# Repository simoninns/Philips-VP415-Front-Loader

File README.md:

# Philips-VP415-Front-Loader
Replacement front-loader module (P) for the Philips VP415 Domesday LaserVision player

For more information, please see [the project wiki](https://github.com/simoninns/Philips-VP415-Front-Loader/wiki)

## Synopsis

This card is designed as a drop-in replacement for the original Philips VP415 LaserVision player's front-loader module (P).

## Motivation

The original front loader module uses custom Philips microswitches which can no longer be sourced.  The front-loader module is responsible for detecting the closure of the disc tray and the switches are impacted everytime a LaserDisc is loaded making it a common failure point in VP415s.  In addition, since the disc tray can vibrate during transport, the front-loader module is often damaged when players are moved.

The new module design is intended to use modern components and act as a drop-in replacement for the original requiring no alteration to the VP415.

## Author

The Philips VP415 replacement front-loader module was designed by Simon Inns.

## License

This project is released under a Creative Commons Attribution-ShareAlike 4.0 International (CC BY-SA 4.0) licence.

You are free to:

Share � copy and redistribute the material in any medium or format
Adapt � remix, transform, and build upon the material
for any purpose, even commercially.

This license is acceptable for Free Cultural Works.

The licensor cannot revoke these freedoms as long as you follow the license terms.

Under the following terms:

Attribution � You must give appropriate credit, provide a link to the license,
and indicate if changes were made. You may do so in any reasonable manner, but
not in any way that suggests the licensor endorses you or your use.

ShareAlike � If you remix, transform, or build upon the material, you must
distribute your contributions under the same license as the original.

No additional restrictions � You may not apply legal terms or technological
measures that legally restrict others from doing anything the license permits.

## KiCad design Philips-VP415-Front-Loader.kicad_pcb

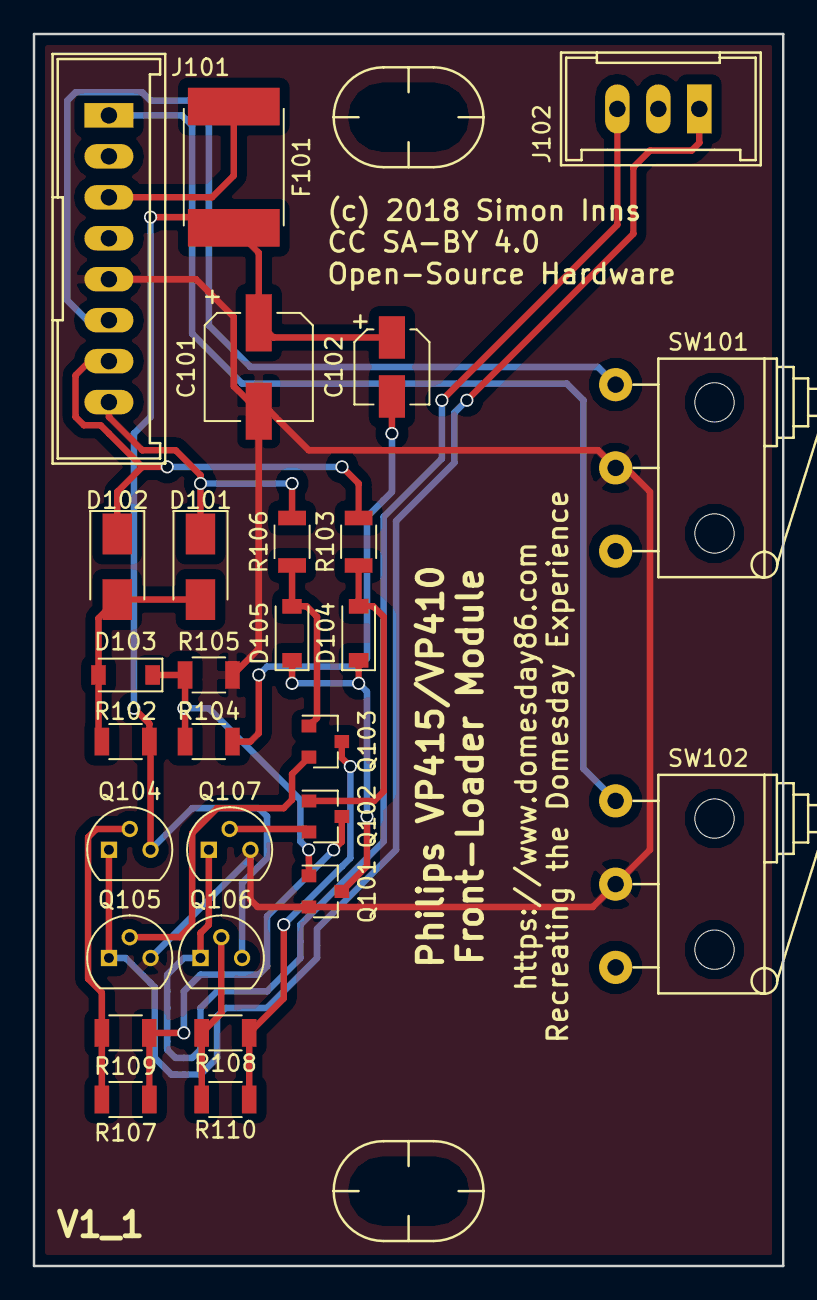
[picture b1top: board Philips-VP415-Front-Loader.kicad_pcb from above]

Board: 2 copper layers, 45.7 x 75.2 mm, 30 parts (0 on the bottom side), 21 nets.

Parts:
C101: 47uF; CP_Elec_6.3x7.7
C102: 4u7; CP_Elec_4x5.3
D101, D102: SS16; D_SMA
D103, D104, D105: 1N4148W; D_SOD-123
F101: 600mA Polyfuse; Fuse_SMD2920
J101: Drive Processor; Lumberg-25-MSF-08
J102: Loader Motor; Lumberg-25-MSF-03
MK101, MK102: Mounting_Hole; Module-P-Mount
Q101, Q102, Q103: BC848C; SOT-23
Q104, Q106: BC327-25; TO-92_Molded_Narrow
Q105, Q107: BC337-25; TO-92_Molded_Narrow
R102, R104, R105: 10K; R_1206
R103, R106: 2K2; R_1206
R107, R108, R109, R110: 750R; R_1206
SW101, SW102: Omron D2HW-BR221DR; D2HW-8BR221DR

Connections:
1P1: J101.1, SW102.2
1P2: J102.1, Q104.1, Q105.1
3P1: F101.1, J101.3
3P2: J102.3, Q106.1, Q107.1
5P1: C101.2, J101.5, Q101.2, Q105.3, Q107.3, R105.1, SW101.3, SW102.3
6P1: J101.6, SW101.2
7P1: D102.1, J101.7, R103.2
8P1: D101.1, J101.8, R106.2
+12V: C101.1, C102.1, F101.2, Q104.3, Q106.3, R102.2
unnamed: C102.2, R104.2
unnamed: D101.2, D102.2, D103.2, R102.1
unnamed: D103.1, Q101.1, R104.1, R105.2
unnamed: D104.1, D105.1, Q101.3
unnamed: D104.2, Q102.1, R103.1
unnamed: D105.2, Q103.1, R106.1
unnamed: Q102.2, Q107.2
unnamed: Q102.3, R107.2, R109.2
unnamed: Q103.2, Q105.2
unnamed: Q103.3, R108.1, R110.1
unnamed: Q104.2, R107.1, R109.1
unnamed: Q106.2, R108.2, R110.2

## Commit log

2018-07-22 Updated license and readme files
2018-07-22 Initial draft of schematic in KiCAD
2018-07-23 Added switch footprint and minor schematic updates
2018-07-23 Added custom mounting holes
2018-07-23 Added Lumberg connector footprints
2018-07-23 Initial layout of major components on PCB
2018-07-23 Finished design ready for testing
2018-07-24 Updates to components and added version number to silkscreen
2018-09-07 Correction to schematic for issue #2 - requires PCB redesign
2018-09-08 Modifications to circuit
    Replaced BD140/BD139s with cheaper BC337/BC327 transistors
    Replaced NFR with SMD polyfuse
2018-09-08 New V1_1 board layout
2022-12-19 Added link to project wiki to the readme file

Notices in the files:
Philips-VP415-Front-Loader.kicad_pcb:
(c)2018 Simon Inns
License: Attribution-ShareAlike 4.0 International (CC BY-SA 4.0)
